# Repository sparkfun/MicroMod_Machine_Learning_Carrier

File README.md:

SparkFun MicroMod Machine Learning Carrier Board
========================================

[*SparkFun MicroMod Machine Learning Carrier Board (16400)*](https://www.sparkfun.com/products/16400)

The MicroMod Machine Learning Carrier Board combines some of the features of our SparkFun Edge Board and SparkFun Artemis boards, but allows you the freedom to explore with any processor in the MicroMod lineup without the need for a central computer or web connection. Voice recognition, always-on voice commands, gesture, or image recognition are possible with TensorFlow applications. The cloud is impressively powerful but all-the-time connection requires power and connectivity that may not be available. Edge computing handles discrete tasks such as determining if someone said "yes" and responds accordingly. The audio analysis is done on the MicroMod combination rather than on the web. This dramatically reduces costs and complexity while limiting potential data privacy leaks. 

This board features two MEMS microphones with an operational amplifier, an ST LIS2DH12 3-axis accelerometer on its own I<sup>2</sup>C bus, a connector to interface to an OV7670 camera (sold separately), and Qwiic connector. A modern USB-C connector makes programming easy and we've exposed the JTAG connector for more advanced users who prefer to use the power and speed of professional tools. We've even added a convenient jumper to measure current consumption for low power testing.

Repository Contents
-------------------

* **/Documentation** - Data sheets, additional product information
* **/Hardware** - Eagle design files (.brd, .sch)
* **/Libraries** - Libraries for use with the <PRODUCT NAME>

Documentation
--------------
* **[Hookup Guide](https://learn.sparkfun.com/tutorials/micromod-machine-learning-carrier-board-hookup-guide)** - Basic hookup guide for the SparkFun MicroMod Machine Learning Carrier Board.
* **[Getting Started with MicroMod](https://learn.sparkfun.com/tutorials/getting-started-with-micromod)** - A tutorial to help you get started with the MicroMod Ecosystem. 
* **[Designing with MicroMod](https://learn.sparkfun.com/tutorials/designing-with-micromod)** - A tutorial to walk you through the specs of the MicroMod processor and carrier board as well as the basics of incorporating the MicroMod form factor into your own PCB designs.

License Information
-------------------

This product is _**open source**_! 

Please review the LICENSE.md file for license information. 

If you have any questions or concerns on licensing, please contact technical support on our [SparkFun forums](https://forum.sparkfun.com/viewforum.php?f=152).

Distributed as-is; no warranty is given.

- Your friends at SparkFun.

_<COLLABORATION CREDIT>_

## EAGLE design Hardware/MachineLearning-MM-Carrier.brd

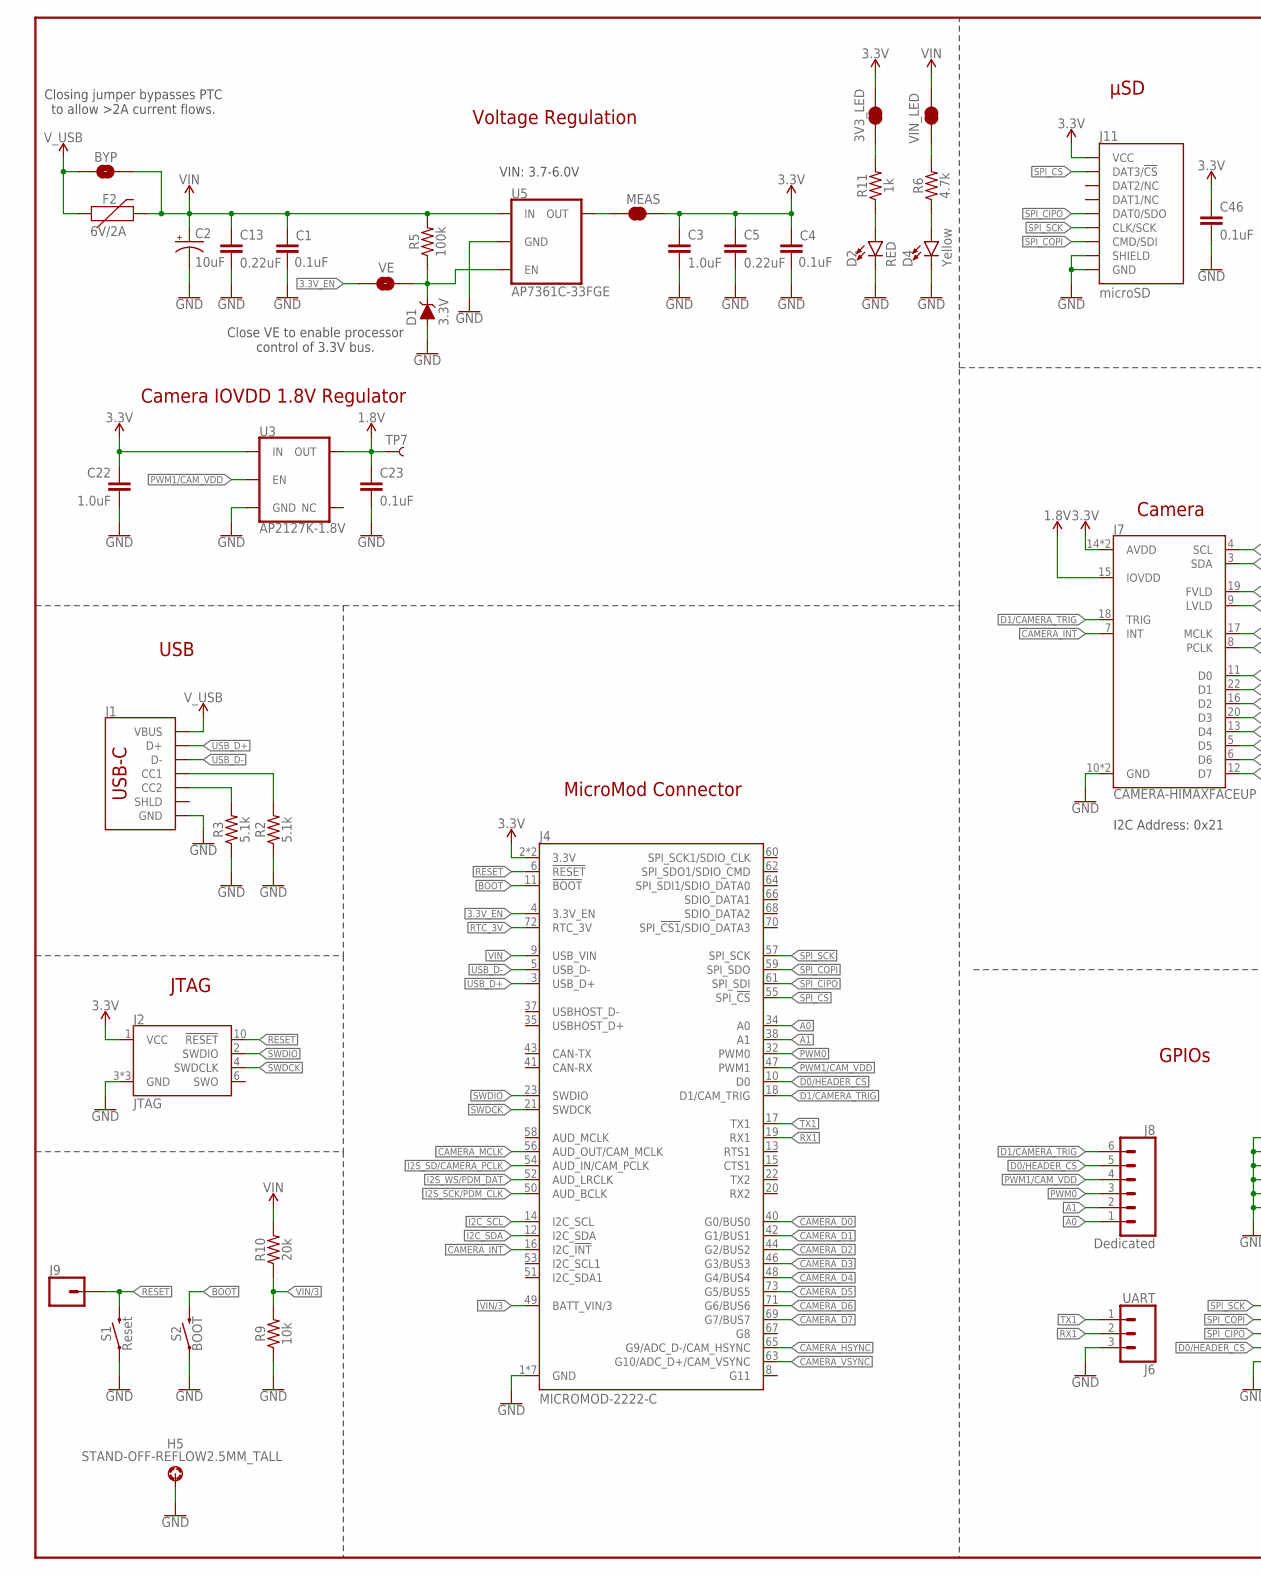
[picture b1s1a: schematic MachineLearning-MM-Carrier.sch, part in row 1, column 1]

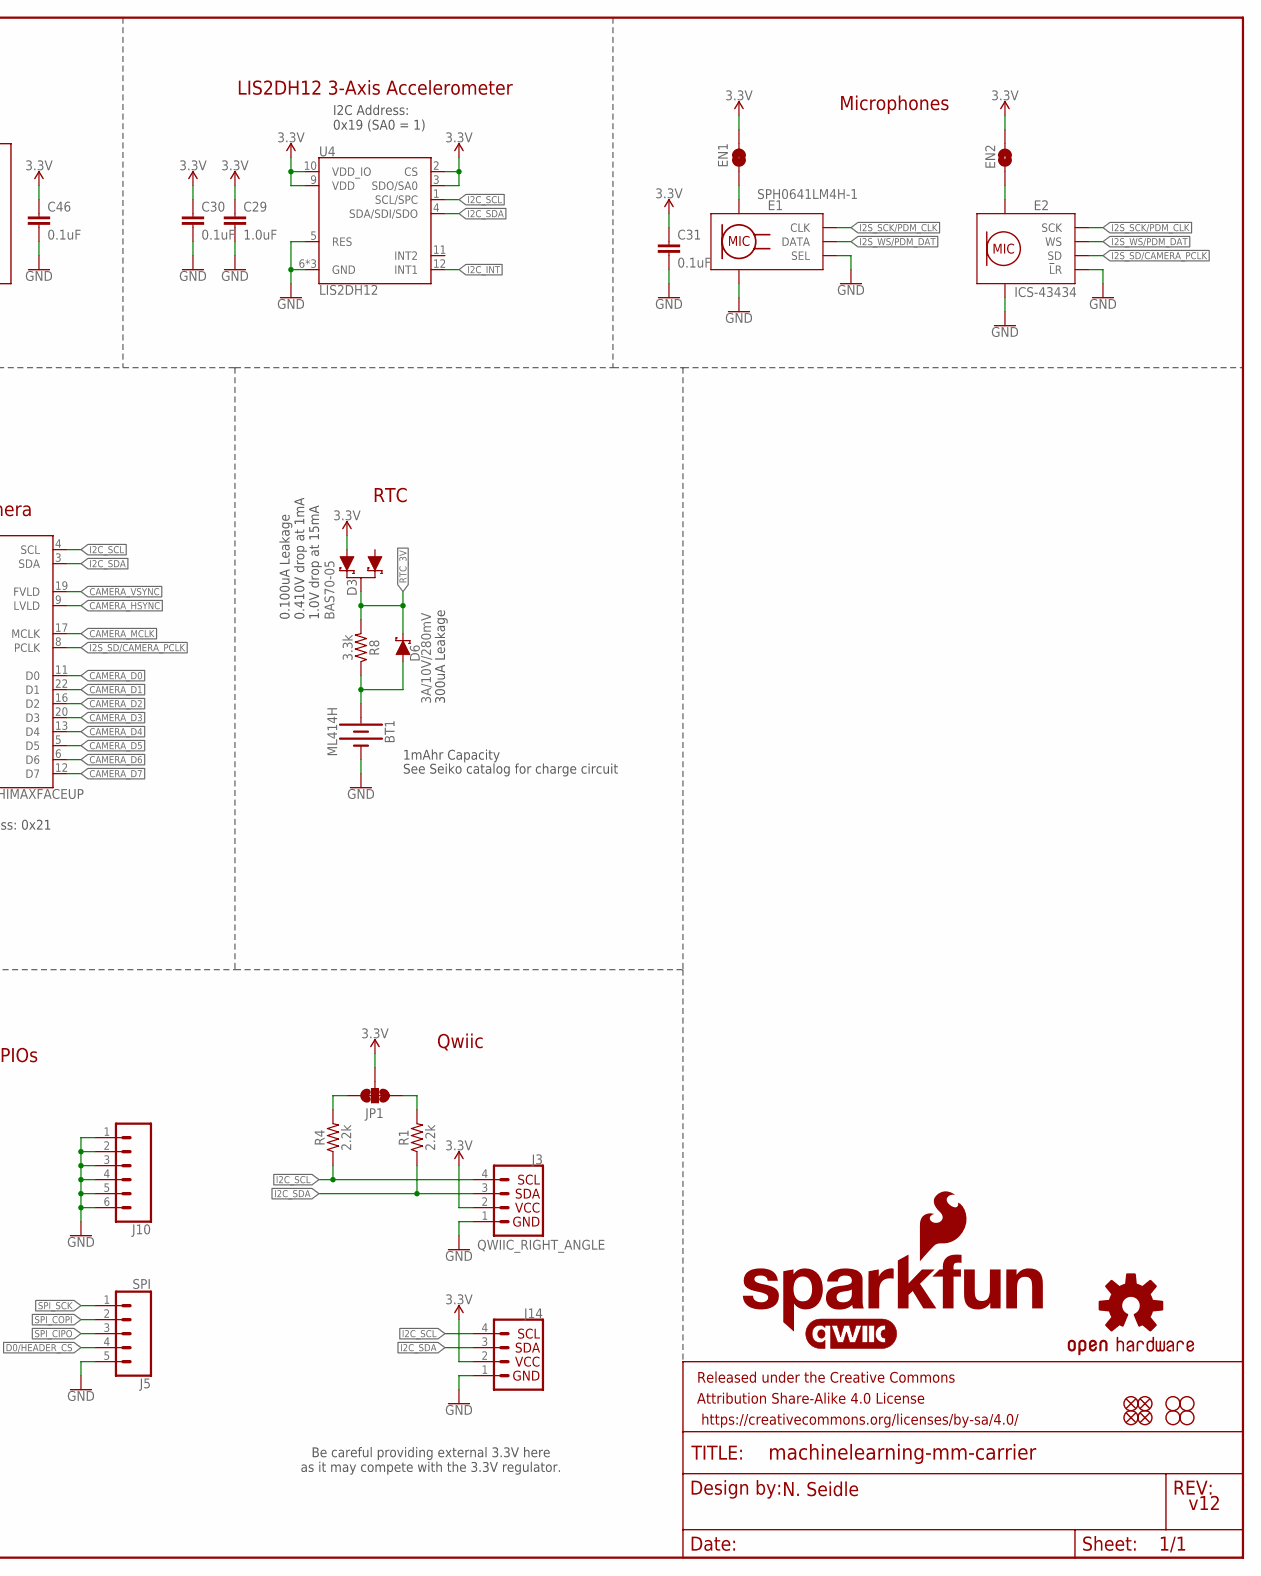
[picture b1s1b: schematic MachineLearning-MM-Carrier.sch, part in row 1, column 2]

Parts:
3V3_LED: JUMPER-SMT_2_NC_TRACE_SILK; SMT-JUMPER_2_NC_TRACE_SILK
BT1: ML414H; ML414H_IV01E
BYP: JUMPER-SMT_2_NO_SILK; SMT-JUMPER_2_NO_SILK
C1, C4, C23, C30, C31, C46: 0.1uF; 0603
C2: 10uF; EIA3216
C3, C22, C29: 1.0uF; 0603
C5, C13: 0.22uF; 0603
D1: 3.3V; SOD-323
D2: RED; LED-0603
D3: BAS70-05; SOT23-3
D4: Yellow; LED-0603
D6: 3A/10V/280mV; SOD-323
E1: SPH0641LM4H-1; SPH0641LM4H-1_MICROPHONE
E2: ICS-43434
EN1: JUMPER-SMT_2_NC_TRACE_SILK; SMT-JUMPER_2_NC_TRACE_SILK
EN2: JUMPER-SMT_2_NO_SILK; SMT-JUMPER_2_NO_SILK
F2: 6V/2A; 1210
FD1, FD2, FD3, FD4: FIDUCIALUFIDUCIAL; FIDUCIAL-MICRO
FRAME1: FRAME-LEDGER; CREATIVE_COMMONS
H1, H2, H3, H4: STAND-OFF
H5: STAND-OFF-REFLOW2.5MM_TALL; STAND-OFF-REFLOW-M2.5
J1: USB_C_2-LAYER_PADS; USB-C-16P-2LAYER-PADS
J2: JTAG; 2X5-PTH-1.27MM
J3: QWIIC_RIGHT_ANGLE; JST04_1MM_RA
J4: MICROMOD-2222-C; M.2-CONNECTOR-E
J5: SPI; 1X05_NO_SILK
J6: UART; 1X03_NO_SILK
J7: CAMERA-HIMAXFACEUP; FPC05024-42201
J8: Dedicated; 1X06_NO_SILK
J9: CONN_01PTH_NO_SILK_YES_STOP; 1X01_NO_SILK
J10: CONN_06NO_SILK_NO_POP; 1X06_NO_SILK
J11: microSD; MICRO-SD-SOCKET
J14: I2C_STANDARD_NO_SILK; 1X04_NO_SILK
JP1: JUMPER-SMT_3_2-NC_TRACE_SILK; SMT-JUMPER_3_2-NC_TRACE_SILK
LOGO1: SFE_LOGO_NAME_FLAME.1_INCH; SFE_LOGO_NAME_FLAME_.1
LOGO2: QWIIC_LOGO_CONNECTOR; QWIIC_5.5MM
LOGO3: OSHW-LOGOMINI; OSHW-LOGO-MINI
MEAS: JUMPER-COMBO_2_NC_TRACE; COMBO-JUMPER_2_NC_TRACE
R1, R4: 2.2k; 0603
R2, R3: 5.1k; 0603
R5: 100k; 0603
R6: 4.7k; 0603
R8: 3.3k; 0603
R9: 10k; 0603
R10: 20k; 0603
R11: 1k; 0603
S1: Reset; TACTILE_SWITCH_SMD_5.2MM
S2: BOOT; TACTILE_SWITCH_SMD_5.2MM
TP7: TEST-POINT3X5; PAD.03X.05
U3: AP2127K-1.8V; SOT23-5
U4: LIS2DH12; LGA-12-LISDH12
U5: AP7361C-33FGE; UDFN-8
VE: JUMPER-SMT_2_NO_SILK; SMT-JUMPER_2_NO_SILK
VIN_LED: JUMPER-SMT_2_NC_TRACE_SILK; SMT-JUMPER_2_NC_TRACE_SILK

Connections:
1.8V: C23.1, J7.15 (IOVDD), TP7.P$1, U3.5 (OUT)
3.3V: 3V3_LED.2, C3.1, C4.1, C5.1, C22.1, C29.1, C30.1, C31.1, C46.1, D3.2 (A1), EN1.2, EN2.2, J2.1 (VCC), J3.2, J4.2 (3.3V), J4.74 (3.3V), J7.14 (AVDD), J7.21 (AVDD), J11.VCC, J14.2, JP1.2, MEAS.2, MEAS.4 (2), U3.1 (IN), U4.2 (CS), U4.3 (SDO/SA0), U4.9 (VDD), U4.10 (VDD_IO)
3.3V_EN: J4.4 (3.3V_EN), VE.1
!BOOT!: J4.11 (!BOOT!), S2.3 (2), S2.4 (2)
!RESET!: J2.10 (!RESET), J4.6 (!RESET!), J9.1, S1.3 (2), S1.4 (2)
A0: J4.34 (A0), J8.1
A1: J4.38 (A1), J8.2
CAMERA_D0: J4.40 (G0/BUS0), J7.11 (D0)
CAMERA_D1: J4.42 (G1/BUS1), J7.22 (D1)
CAMERA_D2: J4.44 (G2/BUS2), J7.16 (D2)
CAMERA_D3: J4.46 (G3/BUS3), J7.20 (D3)
CAMERA_D4: J4.48 (G4/BUS4), J7.13 (D4)
CAMERA_D5: J4.73 (G5/BUS5), J7.5 (D5)
CAMERA_D6: J4.71 (G6/BUS6), J7.6 (D6)
CAMERA_D7: J4.69 (G7/BUS7), J7.12 (D7)
CAMERA_HSYNC: J4.65 (G9/ADC_D-/CAM_HSYNC), J7.9 (LVLD)
CAMERA_INT: J4.16 (I2C_!INT!), J7.7 (INT)
CAMERA_MCLK: J4.56 (AUD_OUT/CAM_MCLK), J7.17 (MCLK)
CAMERA_VSYNC: J4.63 (G10/ADC_D+/CAM_VSYNC), J7.19 (FVLD)
D0/HEADER_!CS!: J4.10 (D0), J5.4, J8.5
D1/CAMERA_TRIG: J4.18 (D1/CAM_TRIG), J7.18 (TRIG), J8.6
GND: BT1.-, C1.2, C2.-, C3.2, C4.2, C5.2, C13.2, C22.2, C23.2, C29.2, C30.2, C31.2, C46.2, D1.A, D2.C, D4.C, E1.2 (SEL), E1.3 (GND), E1.6 (GND), E1.7 (GND), E1.8 (GND), E2.2 (!L!R), E2.3 (GND), E2.7 (GND), E2.8 (GND), E2.9 (GND), H5.1, J1.GND, J1.GND2 (GND), J2.3 (GND), J2.5 (GND), J2.9 (GND), J3.1, J4.1 (GND), J4.7 (GND), J4.33 (GND), J4.36 (GND), J4.39 (GND), J4.45 (GND), J4.75 (GND), J5.5, J6.3, J7.10 (GND), J7.23 (GND), J10.1, J10.2, J10.3, J10.4, J10.5, J10.6, J11.CD1 (SHIELD), J11.GND, J11.GND1 (GND), J11.GND3 (GND), J14.1, R2.1, R3.1, R9.1, S1.1, S1.2 (1), S2.1, S2.2 (1), U3.2 (GND), U4.5 (RES), U4.6 (GND), U4.7 (GND), U4.8 (GND), U5.4 (GND), U5.EP (GND)
I2C_!INT!: U4.12 (INT1)
I2C_SCL: J3.4, J4.14 (I2C_SCL), J7.4 (SCL), J14.4, R4.1, U4.1 (SCL/SPC)
I2C_SDA: J3.3, J4.12 (I2C_SDA), J7.3 (SDA), J14.3, R1.1, U4.4 (SDA/SDI/SDO)
I2S_SCK/PDM_CLK: E1.4 (CLK), E2.4 (SCK), J4.50 (AUD_BCLK)
I2S_SD/CAMERA_PCLK: E2.6 (SD), J4.54 (AUD_IN/CAM_PCLK), J7.8 (PCLK)
I2S_WS/PDM_DAT: E1.1 (DATA), E2.1 (WS), J4.52 (AUD_LRCLK)
unnamed: R6.2, VIN_LED.1
unnamed: JP1.3, R4.2
unnamed: JP1.1, R1.2
unnamed: E1.5 (VDD), EN1.1
unnamed: E2.5 (VDD), EN2.1
unnamed: 3V3_LED.1, R11.2
unnamed: D2.A, R11.1
unnamed: D4.A, R6.1
unnamed: J1.A5 (CC1), R2.2
unnamed: J1.B5 (CC2), R3.2
unnamed: D1.C, R5.1, U5.5 (EN), VE.2
unnamed: BT1.+, D6.A, R8.1
PWM0: J4.32 (PWM0), J8.3
PWM1/CAM_VDD: J4.47 (PWM1), J8.4, U3.3 (EN)
RTC_3V: D3.3 (C), D6.C, J4.72 (RTC_3V), R8.2
RX1: J4.19 (RX1), J6.2
SPI_!CS!: J4.55 (SPI_!CS!), J11.CS/DAT3 (DAT3/!CS!)
SPI_CIPO: J4.61 (SPI_SDI), J5.3, J11.DO/DAT0 (DAT0/SDO)
SPI_COPI: J4.59 (SPI_SDO), J5.2, J11.DI/CMD (CMD/SDI)
SPI_SCK: J4.57 (SPI_SCK), J5.1, J11.SCLK (CLK/SCK)
SWDCK: J2.4 (SWDCLK), J4.21 (SWDCK)
SWDIO: J2.2 (SWDIO), J4.23 (SWDIO)
TX1: J4.17 (TX1), J6.1
USB_D+: J1.A6 (D+), J1.B6 (D+), J4.3 (USB_D+)
USB_D-: J1.A7 (D-), J1.B7 (D-), J4.5 (USB_D-)
VIN: BYP.2, C1.1, C2.+, C13.1, F2.2, J4.9 (USB_VIN), R5.2, R10.2, U5.8 (IN), VIN_LED.2
VIN/3: J4.49 (BATT_VIN/3), R9.2, R10.1
VREG_3.3V: MEAS.1, MEAS.3 (1), U5.1 (OUT)
V_USB: BYP.1, F2.1, J1.VBUS1 (VBUS), J1.VBUS2 (VBUS)

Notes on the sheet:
LIS2DH12 3-Axis Accelerometer
I2C Address: 0x19 (SA0 = 1)
I2C Address: 0x21
μSD
300uA Leakage
See Seiko catalog for charge circuit
1mAhr Capacity
Closing jumper bypasses PTC to allow >2A current flows.
JTAG
Camera IOVDD 1.8V Regulator
USB
GPIOs
Camera
Microphones
Qwiic
RTC
Voltage Regulation
MicroMod Connector
0.100uA Leakage 0.410V drop at 1mA 1.0V drop at 15mA
N. Seidle
v12
VIN: 3.7-6.0V
Be careful providing external 3.3V here as it may compete with the 3.3V regulator.
Close VE to enable processor control of 3.3V bus.

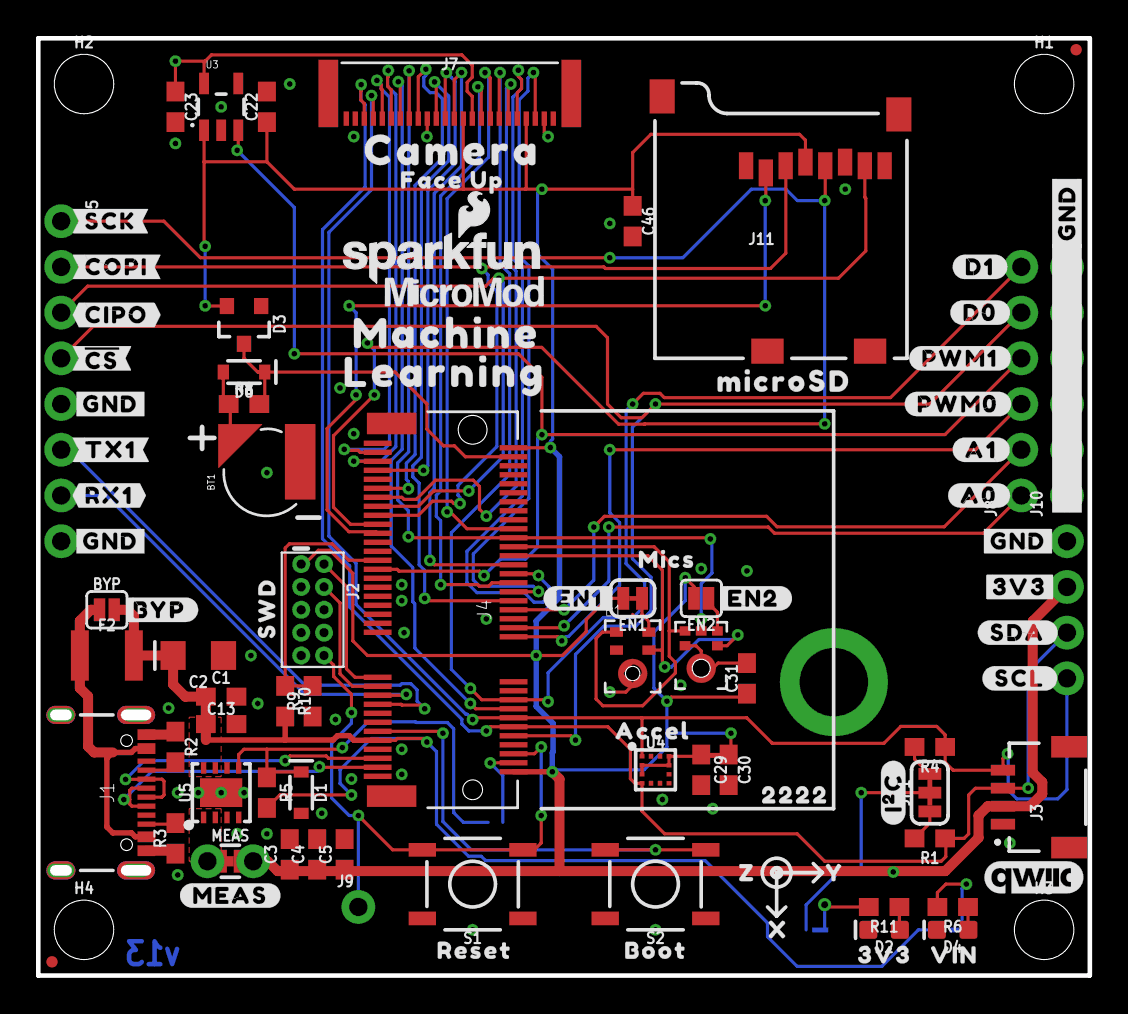
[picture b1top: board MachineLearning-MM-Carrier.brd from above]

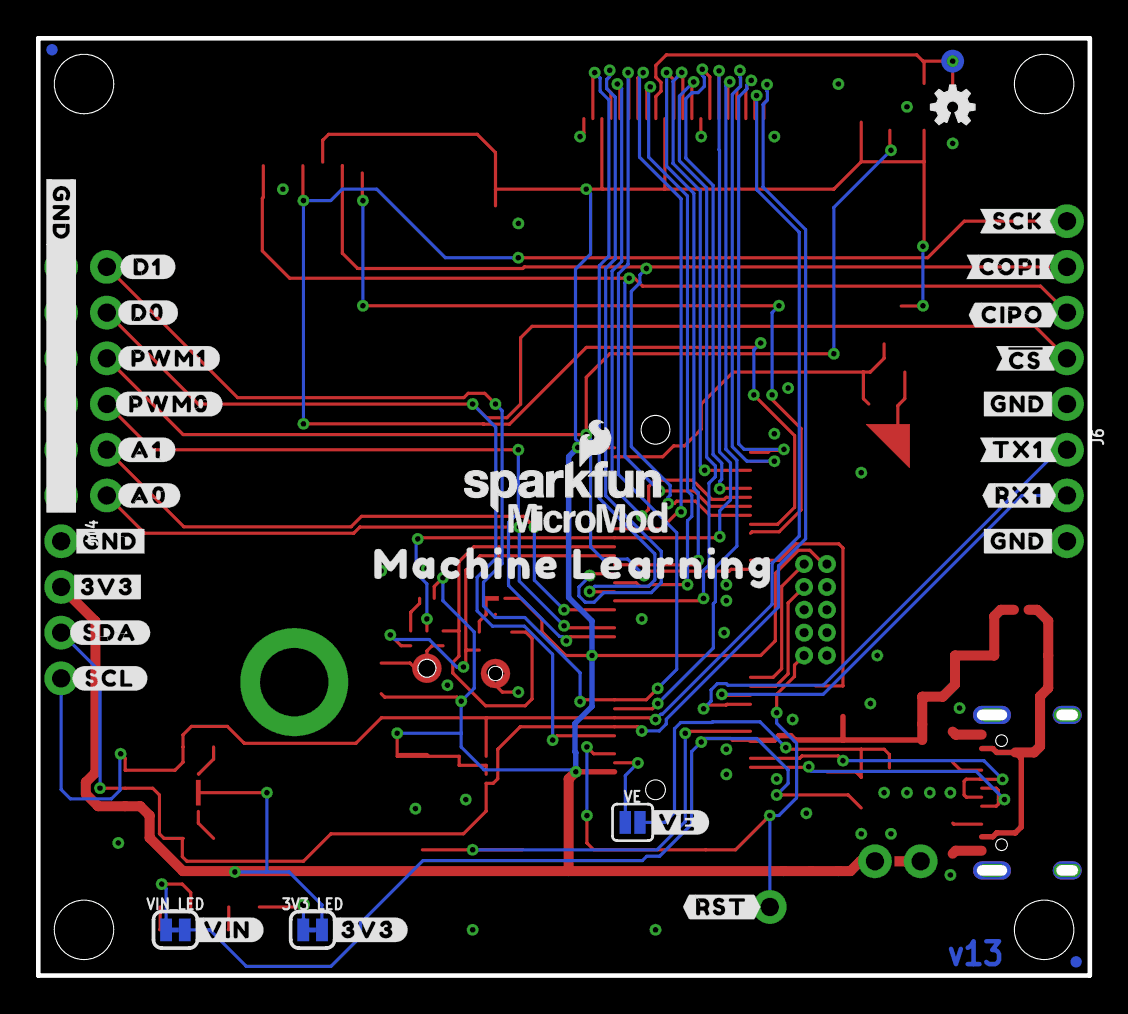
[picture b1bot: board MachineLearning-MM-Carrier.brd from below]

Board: 2 copper layers, 58.1 x 51.7 mm, 138 parts (36 on the bottom side), 56 nets.

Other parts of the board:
LOGO4: SFE_LOGO_NAME_FLAME.1_INCH; SFE_LOGO_NAME_FLAME_.1
U$1: #EN1#3
U$2: #EN2#4
U$3: CAMERA0
U$4: #3V3#0
U$5: MICS0
U$6, U$7: #A0#5
U$8, U$9: #A1#4
U$10, U$25: #D0#1
U$11, U$12, U$15, U$16: #GND#0
U$13, U$14: #3V3#1
U$17: #RST#1
U$18: #VE#0
U$19: #MEAS#2
U$20: #VIN#1
U$21: SWD0
U$22: FACE_UP0
U$23: #I�C#0
U$24, U$34: MICROMOD_LOGO_.35
U$26, U$37: MACHINE0
U$27, U$30: LEARNING1
U$28: MICROSD0
U$29, U$31: #D1#0
U$32, U$41: #PWM0#3
U$33: #BYP#1
U$35, U$68: ##CS##3
U$36: 3V37
U$38: 22223
U$39: ACCEL4
U$40: BOOT5
U$42, U$49: #PWM1#2
U$43, U$44: #SCL#3
U$45: RESET6
U$46: VIN8
U$47: X1
U$48: Y2
U$50, U$51: #SDA#2
U$52: Z0
U$69, U$70: #CIPO#2
U$71, U$72: #COPI#1
U$73, U$74, U$81, U$82: #GND#4
U$75, U$76: #RX1#6
U$77, U$78: #SCK#0
U$79, U$80: #TX1#5

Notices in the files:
parts and their libraries:
SparkFun-Aesthetics: Licensing: Creative Commons ShareAlike 4.0 International - https://creativecommons.org/licenses/by-sa/4.0
SparkFun-Aesthetics: Released under the Creative Commons Attribution Share-Alike 4.0 License
SparkFun-Aesthetics: https://creativecommons.org/licenses/by-sa/4.0
